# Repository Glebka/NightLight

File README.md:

# NightLight

This is device that will shade some light on your road to the kitchen at night :)

Well, this is simple electric LED light that powers from small Li-Pol cell (around 60 mAh capacity).

It supports three modes:
- **Off** - no light, charging enabled
- **Always on** - light always on
- **On for a period of time after motion detected** - yep, I've integrated a cheap microwave motion detector. When it triggers - the light turns on for approximately 3 minutes (that is enough time to grab something tasty in the kitchen and get back) and then turns off automatically.

## 3D View

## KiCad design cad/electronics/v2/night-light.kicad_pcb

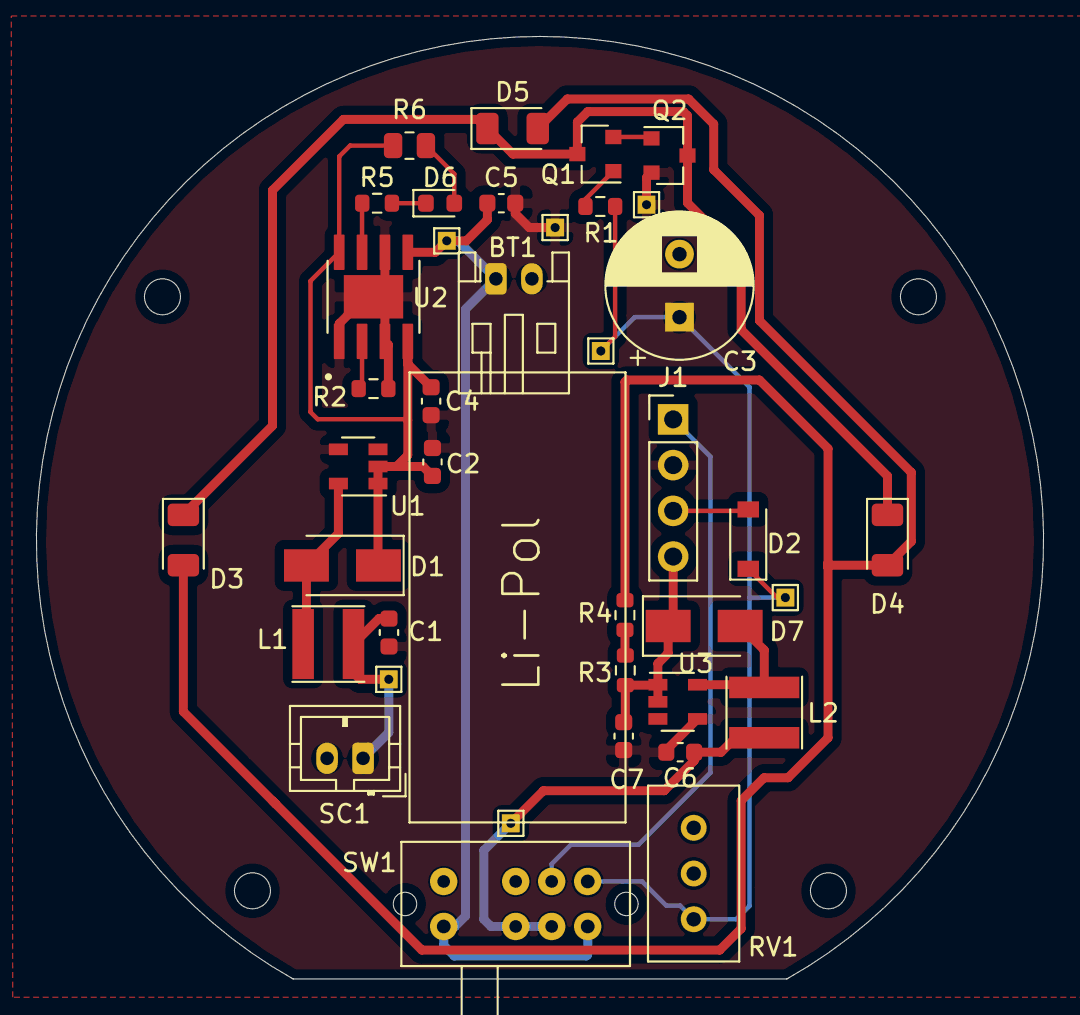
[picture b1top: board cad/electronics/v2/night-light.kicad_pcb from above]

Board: 2 copper layers, 55.9 x 52.4 mm, 32 parts (0 on the bottom side), 20 nets.

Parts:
BT1: LiPol,60mAh; JST_PH_S2B-PH-K_1x02_P2.00mm_Horizontal
C1, C2, C6, C7: 4.7uF; C_0603_1608Metric
C3: 470uF; CP_Radial_D8.0mm_P3.50mm
C4, C5: 10uF; C_0603_1608Metric
D1, D7: SS14; D_SMA
D2: 1N5819; D_SOD-123
D3, D4, D5: LED; LED_1206_3216Metric
D6: LED-Y; LED_0603_1608Metric
J1: RWCL-0516; PinHeader_1x04_P2.54mm_Vertical
L1, L2: 47uH; L_Taiyo-Yuden_NR-40xx
Q1, Q2: MMBT3904; SOT-23
R1: 470k; R_0603_1608Metric
R2: 18k; R_0603_1608Metric
R3: 150R; R_0603_1608Metric
R4: 82R; R_0603_1608Metric
R5: 3k; R_0603_1608Metric
R6: 0R; R_0805_2012Metric
RV1: BAOTER 3296; Potentiometer_Bourns_3296W_Vertical
SC1: 5V, 0.125W; JST_PH_B2B-PH-K_1x02_P2.00mm_Vertical
SW1: L-KLS7-SK35-23D07-VG3
U1, U3: NCP1402SN50T1G; SOT-23-5
U2: TP4056; SOP127P600X175-9N

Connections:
3V3: J1.1, SW1.7
5V: C7.1, D7.1, J1.4, R3.1, U3.1, U3.2
A_ON: C3.1, D2.1, R1.2, RV1.1, SW1.8
BAT+: C6.1, L2.1, SW1.2, SW1.3
CH_IN: C2.1, C4.2, D1.1, R6.2, U1.1, U1.2, U2.4, U2.8
GND: BT1.2, C1.2, C2.2, C3.2, C4.1, C5.2, C6.2, C7.2, J1.2, Q2.2, R2.1, RV1.2, SC1.2, U1.4, U2.1, U2.3, U2.6, U2.9, U3.4
MOTION: D2.2, J1.3
unnamed: C1.1, L1.1, SC1.1
unnamed: D1.2, L1.2, U1.5
unnamed: D3.1, D4.1, D5.1, Q1.3, Q2.3
unnamed: D3.2, D4.2, D5.2, R4.2
unnamed: D6.1, R5.2
unnamed: D6.2, R6.1
unnamed: D7.2, L2.2, U3.5
unnamed: Q1.1, R1.1
unnamed: Q1.2, Q2.1
unnamed: R2.2, U2.2
unnamed: R3.2, R4.1
unnamed: R5.1, U2.7
VBAT: BT1.1, C5.1, SW1.1, SW1.4, U2.5

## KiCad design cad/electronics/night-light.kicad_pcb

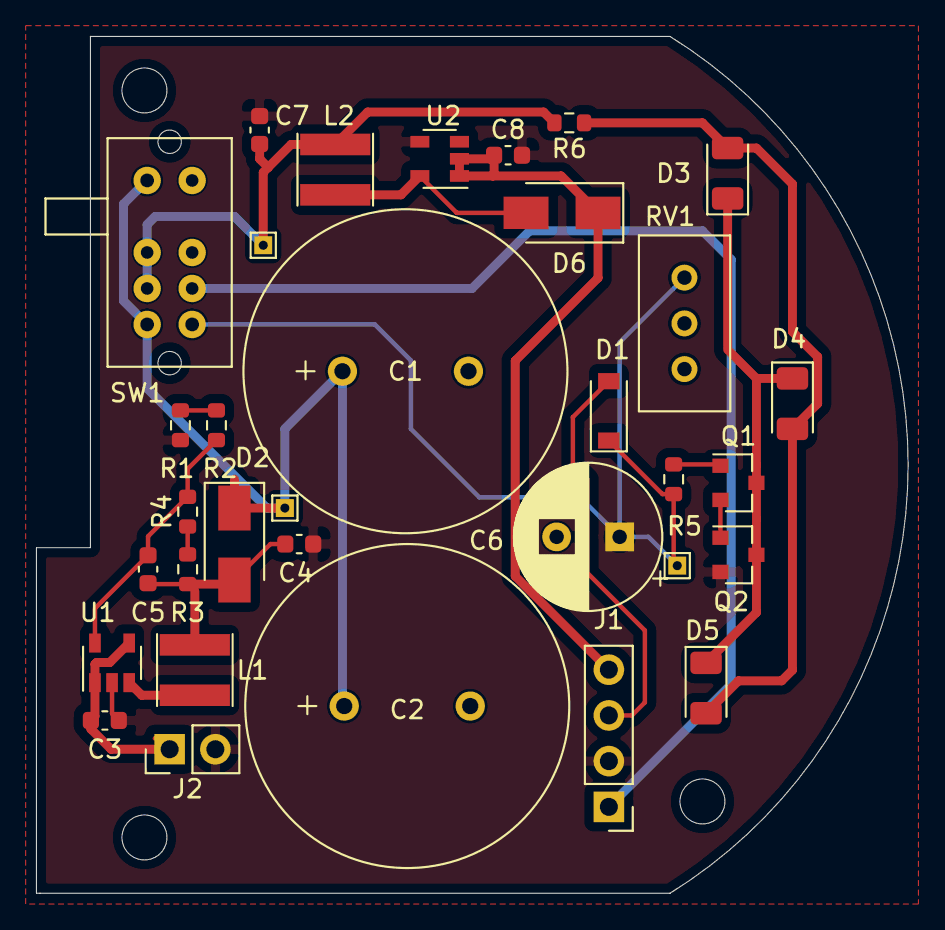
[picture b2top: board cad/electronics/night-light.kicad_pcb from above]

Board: 2 copper layers, 48.4 x 47.6 mm, 30 parts (0 on the bottom side), 18 nets.

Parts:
C1, C2: 50F; SMAXON-DRL-2.7V-50F
C3, C4, C7, C8: 4.7uF; C_0603_1608Metric
C5: 1nF(102); C_0603_1608Metric
C6: 470uF; CP_Radial_D8.0mm_P3.50mm
D1: 1N5819; D_SOD-123
D2, D6: SS14; D_SMA
D3, D4, D5: LED; LED_1206_3216Metric
J1: RWCL-0516; PinHeader_1x04_P2.54mm_Vertical
J2: Solar Cell; PinHeader_1x02_P2.54mm_Vertical
L1: 4.7uH; L_Taiyo-Yuden_NR-40xx
L2: 47uH; L_Taiyo-Yuden_NR-40xx
Q1, Q2: MMBT3904; SOT-23
R1: 51k; R_0603_1608Metric
R2, R4: 200k; R_0603_1608Metric
R3: 680k; R_0603_1608Metric
R5: 470k; R_0603_1608Metric
R6: 62; R_0603_1608Metric
RV1: BAOTER 3296; Potentiometer_Bourns_3296W_Vertical
SW1: L-KLS7-SK35-23D07-VG3
U1: NCP1529A; SOT-23-5
U2: NCP1402SN50T1G; SOT-23-5

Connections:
+3V3: J1.1, SW1.7
+5V: C8.1, D6.1, J1.4, U2.1, U2.2
A_ON: C6.1, D1.1, R5.2, RV1.1, SW1.8
BAT+: C7.1, L2.1, R6.2, SW1.2, SW1.3
MOTION: D1.2, J1.3
unnamed: C4.2, C5.1, D2.2, L1.2, R3.1
unnamed: C5.2, R2.1, R4.2, U1.5
unnamed: D3.1, D4.1, D5.1, Q1.3, Q2.3
unnamed: D3.2, D4.2, D5.2, R6.1
unnamed: D6.2, L2.2, U2.5
unnamed: L1.1, U1.3
unnamed: Q1.1, R5.1
unnamed: Q1.2, Q2.1
unnamed: R1.1, R2.2
unnamed: R3.2, R4.1
SOL+: C3.1, J2.1, U1.1, U1.4
SOL-: C1.2, C2.2, C3.2, C4.1, C6.2, C7.2, C8.2, J1.2, J2.2, Q2.2, R1.2, RV1.2, U1.2, U2.4
Vch: C1.1, C2.1, D2.1, SW1.1, SW1.4

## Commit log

2022-05-30 Add LICENSE
2022-06-03 Imlement device v2 with Li-Pol battery
2022-06-19 Update files according to latest design
2022-06-19 Add README with images
